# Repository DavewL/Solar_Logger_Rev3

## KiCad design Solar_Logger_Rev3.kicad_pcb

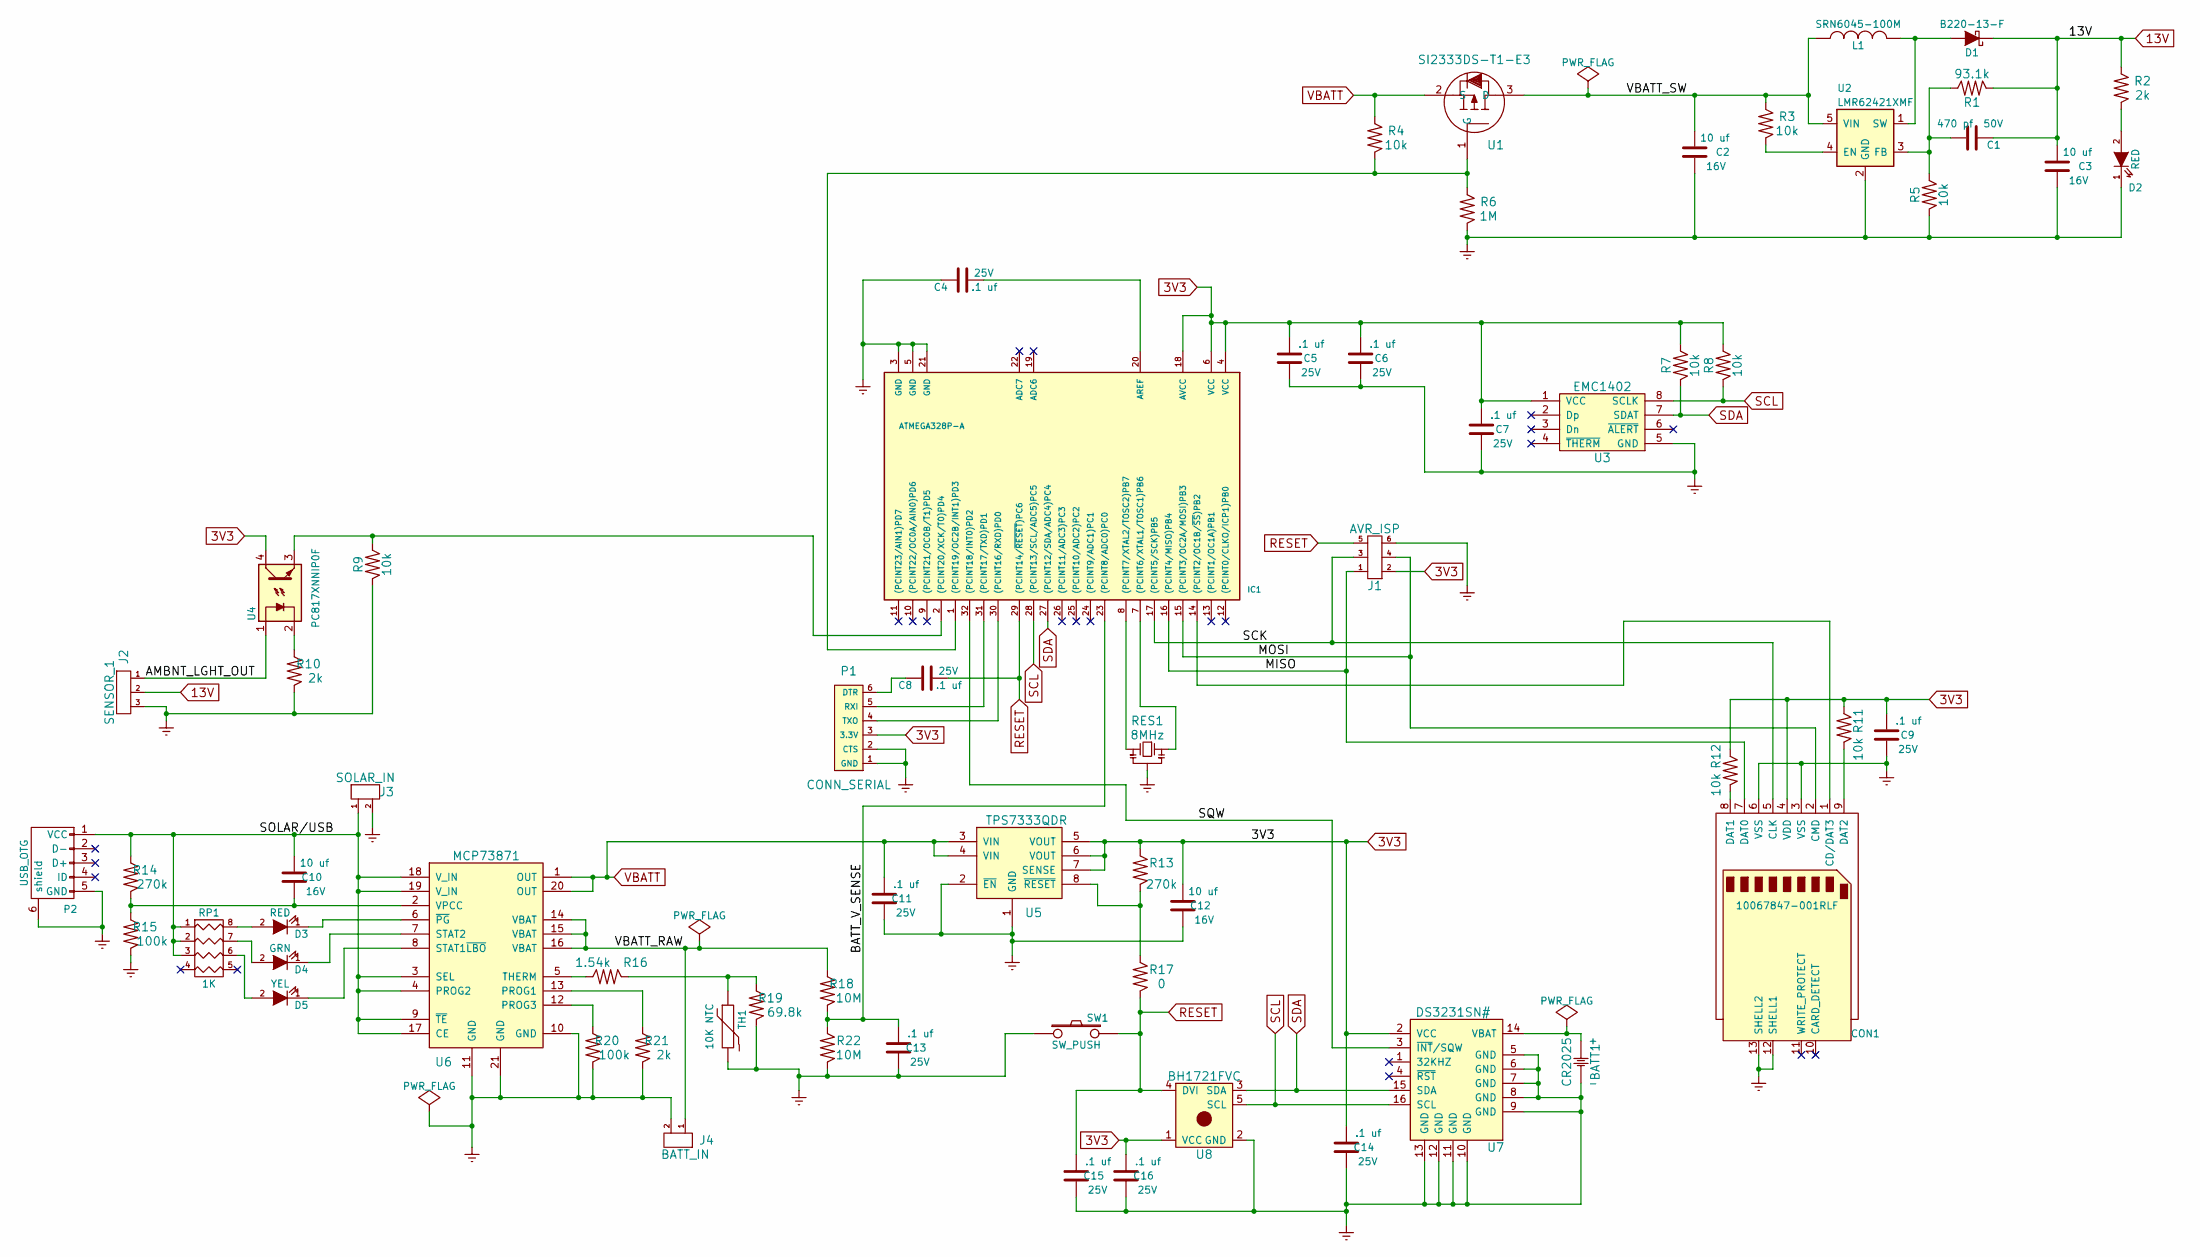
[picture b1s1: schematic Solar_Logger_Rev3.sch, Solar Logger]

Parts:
BATT1: CR2025; C2025; PartNumber BAT-HLD-001
C1: 470 pf; C_0805_HandSoldering; Voltage 50V
C2, C3, C10, C12: 10 uf; R_1206_HandSoldering; Voltage 16V; PartNumber C3216X5R1C106K160AA
C4, C5, C6, C7, C8, C9, C11, C13, C14, C15, C16: .1 uf; C_0805_HandSoldering; Voltage 25V; PartNumber GRM216F51E104ZA01D
CON1: 10067847-001RLF; SD_Card_Receptacle_DL
D1: B220-13-F; SMB_Handsoldering
D2, D3: RED; R_0805_HandSoldering; PartNumber CMD17-21VRC/TR8
D4: GRN; R_0805_HandSoldering; PartNumber CMD17-21VGC/TR8
D5: YEL; R_0805_HandSoldering; PartNumber CMD17-21VYD/TR8
IC1: ATMEGA328P-A; TQFP-32_7x7mm_Pitch0.8mm
J1: AVR_ISP; Pin_Header_Straight_2x03
J2: SENSOR_1; b3b-ph-kl; PartNumber B3B-PH-K-S(LF)(SN)
J3: SOLAR_IN; s2b-ph-kl
J4: BATT_IN; s2b-ph-kl
L1: SRN6045-100M; inductor_smd_5.8x2.8mm
P1: CONN_SERIAL; Pin_Header_Straight_1x06
P2: USB_OTG; USB_MICRO_VERT; PartNumber 614105150721
R1: 93.1k; R_0805_HandSoldering; PartNumber ERJ-6ENF9312V
R2, R10, R21: 2k; R_0805_HandSoldering; PartNumber ERJ-6ENF2001V
R3, R4, R5, R7, R8, R9, R11, R12: 10k; R_0805_HandSoldering; PartNumber ERJ-6ENF1002V
R6: 1M; R_0805_HandSoldering; PartNumber ERJ-6GEYJ105V
R13, R14: 270k; R_0805_HandSoldering; PartNumber ERJ-6ENF2703V
R15, R20: 100k; R_0805_HandSoldering; PartNumber RC0805FR-07100KL
R16: 1.54k; R_0805_HandSoldering; PartNumber ERJ-6ENF1541V
R17: 0; R_0805_HandSoldering; PartNumber 0
R18, R22: 10M; R_0805_HandSoldering; PartNumber RC0805FR-0710ML
R19: 69.8k; R_0805_HandSoldering; PartNumber ERJ-6ENF6982V
RES1: 8MHz; Resonator_7.2x3mm
RP1: 1K; R_Array_Convex_4x1206; PartNumber EXB-38V102JV
SW1: SW_PUSH; PUSHBUTTON_SMD_2PIN
TH1: 10K NTC; do214ac; PartNumber MM103J1F
U1: SI2333DS-T1-E3; SOT-23_Handsoldering
U2: LMR62421XMF; SOT-23-5
U3: EMC1402; MSOP-8_3x3mm_Pitch0.65mm
U4: PC817XNNIP0F; mdip_4
U5: TPS7333QDR; SOIC-8_3.9x4.9mm_Pitch1.27mm
U6: MCP73871; qfn-20
U7: DS3231SN#; SOIC-16_7.5x10.3mm_Pitch1.27mm
U8: BH1721FVC; WSOF5

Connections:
3V3: C5.2, C6.2, C7.2, C9.2, C12.2, C14.2, C16.2, CON1.4 (VDD), IC1.4 (VCC), IC1.6 (VCC), IC1.18 (AVCC), J1.2, P1.3 (3.3V), R7.1 (A), R8.1 (A), R11.1 (A), R12.1 (A), R13.1 (A), U3.1 (VCC), U4.4, U5.5 (VOUT), U5.6 (VOUT), U5.7 (SENSE), U7.2 (VCC), U8.1 (VCC)
13V: C1.1, C3.2, D1.1 (K), J2.2, R1.2 (K), R2.1 (A)
/AMBNT_LGHT_OUT: J2.1, U4.1
/BATT_V_SENSE: C13.2, IC1.23 ((PCINT8/ADC0)PC0), R18.2 (K), R22.1 (A)
/MISO: CON1.7 (DAT0), IC1.16 ((PCINT4/MISO)PB4), J1.1
/MOSI: CON1.2 (CMD), IC1.15 ((PCINT3/OC2A/MOSI)PB3), J1.4
/SCK: CON1.5 (CLK), IC1.17 ((PCINT5/SCK)PB5), J1.3
/SOLAR/USB: C10.2, J3.1, P2.1 (VCC), R14.1 (A), RP1.1, RP1.2, RP1.3, U6.3 (SEL), U6.4 (PROG2), U6.9 (~TE), U6.17 (CE), U6.18 (V_IN), U6.19 (V_IN)
/SQW: IC1.32 ((PCINT18/INT0)PD2), U7.3 (~INT~/SQW)
/VBATT_RAW: J4.1, R18.1 (A), U6.14 (VBAT), U6.15 (VBAT), U6.16 (VBAT)
/VBATT_SW: C2.2, L1.1, R3.1 (A), U1.3 (D), U2.5 (VIN)
Earth: BATT1.2 (-), C2.1, C3.1, C4.1, C5.1, C6.1, C7.1, C9.1, C11.1, C12.1, C13.1, C14.1, C15.1, C16.1, CON1.3 (VSS), CON1.6 (VSS), CON1.12 (SHELL1), CON1.13 (SHELL2), D2.1 (K), IC1.3 (GND), IC1.5 (GND), IC1.21 (GND), J1.6, J2.3, J3.2, J4.2, P1.1 (GND), P1.2 (CTS), P2.5 (GND), P2.6 (shield), R5.2 (K), R6.2 (K), R9.2 (K), R10.2 (K), R15.2 (K), R19.2 (K), R20.2 (K), R21.2 (K), R22.2 (K), RES1.2, SW1.1, TH1.2, U2.2 (GND), U3.5 (GND), U5.1 (GND), U5.2 (~EN), U6.10 (GND), U6.11 (GND), U6.21 (GND), U7.5 (GND), U7.6 (GND), U7.7 (GND), U7.8 (GND), U7.9 (GND), U7.10 (GND), U7.11 (GND), U7.12 (GND), U7.13 (GND), U8.2 (GND)
unnamed: BATT1.1 (+), U7.14 (VBAT)
unnamed: C1.2, R1.1 (A), R5.1 (A), U2.3 (FB)
unnamed: C4.2, IC1.20 (AREF)
unnamed: C8.1, P1.6 (DTR)
unnamed: C10.1, R14.2 (K), R15.1 (A), U6.2 (VPCC)
unnamed: CON1.1 (CD/DAT3), IC1.14 ((PCINT2/OC1B/~SS~)PB2)
unnamed: CON1.8 (DAT1), R12.2 (K)
unnamed: CON1.9 (DAT2), R11.2 (K)
unnamed: D1.2 (A), L1.2, U2.1 (SW)
unnamed: D2.2 (A), R2.2 (K)
unnamed: D3.1 (K), U6.6 (~PG)
unnamed: D3.2 (A), RP1.8 (R1)
unnamed: D4.1 (K), U6.7 (STAT2)
unnamed: D4.2 (A), RP1.7 (R2)
unnamed: D5.1 (K), U6.8 (STAT1~LBO)
unnamed: D5.2 (A), RP1.6 (R3)
unnamed: IC1.1 ((PCINT19/OC2B/INT1)PD3), R4.2 (K), R6.1 (A), U1.1 (G)
unnamed: IC1.2 ((PCINT20/XCK/T0)PD4), R9.1 (A), U4.3
unnamed: IC1.7 ((PCINT6/XTAL1/TOSC1)PB6), RES1.3
unnamed: IC1.8 ((PCINT7/XTAL2/TOSC2)PB7), RES1.1
unnamed: IC1.30 ((PCINT16/RXD)PD0), P1.4 (TXO)
unnamed: IC1.31 ((PCINT17/TXD)PD1), P1.5 (RXI)
unnamed: R3.2 (K), U2.4 (EN)
unnamed: R10.1 (A), U4.2
unnamed: R13.2 (K), R17.1 (A), U5.8 (~RESET)
unnamed: R16.1 (A), U6.5 (THERM)
unnamed: R16.2 (K), R19.1 (A), TH1.1
unnamed: R20.1 (A), U6.12 (PROG3)
unnamed: R21.1 (A), U6.13 (PROG1)
RESET: C8.2, C15.2, IC1.29 ((PCINT14/~RESET~)PC6), J1.5, R17.2 (K), SW1.2, U8.4 (DVI)
SCL: IC1.28 ((PCINT13/SCL/ADC5)PC5), R8.2 (K), U3.8 (SCLK), U7.16 (SCL), U8.5 (SCL)
SDA: IC1.27 ((PCINT12/SDA/ADC4)PC4), R7.2 (K), U3.7 (SDAT), U7.15 (SDA), U8.3 (SDA)
VBATT: C11.2, R4.1 (A), U1.2 (S), U5.3 (VIN), U5.4 (VIN), U6.1 (OUT), U6.20 (OUT)

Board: 2 copper layers, 65 parts (12 on the bottom side), 45 nets, no tracks yet.

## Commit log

2015-08-17 :lollipop: Added .gitattributes & .gitignore files
2015-08-17 Design Files
